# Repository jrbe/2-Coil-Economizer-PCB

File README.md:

**This V1.1 version is not working.  The transistor is flipped on each channel and the DRV103's I got seem to be counterfeit.  Plan is to eventually swap both DRV103's to 556 timers and to a logic ic for flexible input control to reduce cost, eliminate the DRV issues, and simplify the whole project.**

# 2 Coil Economizer PCB
 This 2 Coil DRV103 Economizer PCB is not tested yet. It has at least 1 issue as when its soldered to + triggered the coil output is at 100% with the trigger wire floating. 

It was designed for contactor economizing, for 8-28v, and around 10 amps for each coil. This delivers full power for a short time to pull in the relay or contactor then switches over to a pulse output to conserve power, lower heat, etc. for the coil.

The frequency, duty cycle, and delay info is printed on the bottom of the pc board for reference.

Frequency is set to 25kHz by default.  Its recommended to keep it at 25kHz but can be adjusted from 25kHz down to 20kHz by cutting the 20/25kHz jumpers if required. The 20kHZ mod jumper (follow the silkscreen line to it) must also be soldered to adjust the voltage divider stack to work with the different pwm frequency load requirements of 20kHz for the DRV103 IC.

PWM Duty cycle is set to 21.8% by default, 3 jumpers are shorted on each coil circuit.  This is using voltage to set the duty cycle in the DRV103, a simulation of the circuit is here, https://everycircuit.com/circuit/4973018295828480  These can be cut if necessary.  If more than 21.8% is required more solder jumpers can be soldered.  Which gets cut or soldered doesn't matter as long as its in the silkscreened group. 
Number of jumpers shorted: 0 = 14.3%, 1 = 17%, 2 = 19.75%, 3 = 21.8%, 4 = 23.9%, 5 = 26%, 6 = 28%.  Looking at the top, the left 3 are shorted with a trace across them.

The DRV103 has an adjustable full on time then switches to pwm to hold the coil.  By default all 4 solder jumpers are shorted for a 550ms on time.  These jumpers can be cut to allow less full on time if required. Which gets cut or soldered doesn't matter as long as its in the silkscreened group.
Number of jumpers shorted: 0 = 110ms, 1 = 220ms, 2 = 330ms, 3 = 440ms, 4 = 550ms.

There is a trigger +/- jumper for each coil that needs to be soldered center pad to + or -.  Soldered to + it will turn on the coil with a + signal connected to Coil x trigger.  Soldered to -, it will turn on when the coil trigger is connected to -.  https://everycircuit.com/circuit/4812355044900864 is a simulation of the circuit.

There is an excel file with the calculated values of different DRV103 settings in the references folder.  

The oval slots are oversized for both 5mm and 5.08mm connectors.  This includes Phoenix Contact 1017509, 1751228, 1776260-8, etc. TE 521384-8, Faston tabs, and direct solder.  If direct solder is chosen the "teeth" at the bottom can be used as a strain relief with shrink tubing over them. They are 8mm wide at the bottom.  Small or single wires may require a second layer of shrink tubing.

Testing of the contactors should be done without high voltage connected.  A voltage of 10v or less should be considered for testing to verify the contactors will not accidently open from a low 12v battery. Watching for continuity the coil can be energized and running in pwm mode and hit down on a padded table (simulating a hard bump) with the high voltage terminals up.  There should be no break in continuity and should not open.

Pricey items are the tantalum capacitors that are recommended in the Ti DRV103 datasheet for higher power useage and a few extended JLC components with uncommon resistances.  The DRV103 ICs will likely need to be preordered from JLCPCB or populated later.  

These boards were about $30usd each from JLCPCB at a qty of 5 boards at the time of design.  
Designed in KiCAD 7 
Production files were made using Fabrication Toolkit, https://github.com/bennymeg/Fabrication-Toolkit to correct BOMs, rotations, etc. for JLCPCB.
https://yaqwsx.github.io/jlcparts/#/ was used to find available JLC components.

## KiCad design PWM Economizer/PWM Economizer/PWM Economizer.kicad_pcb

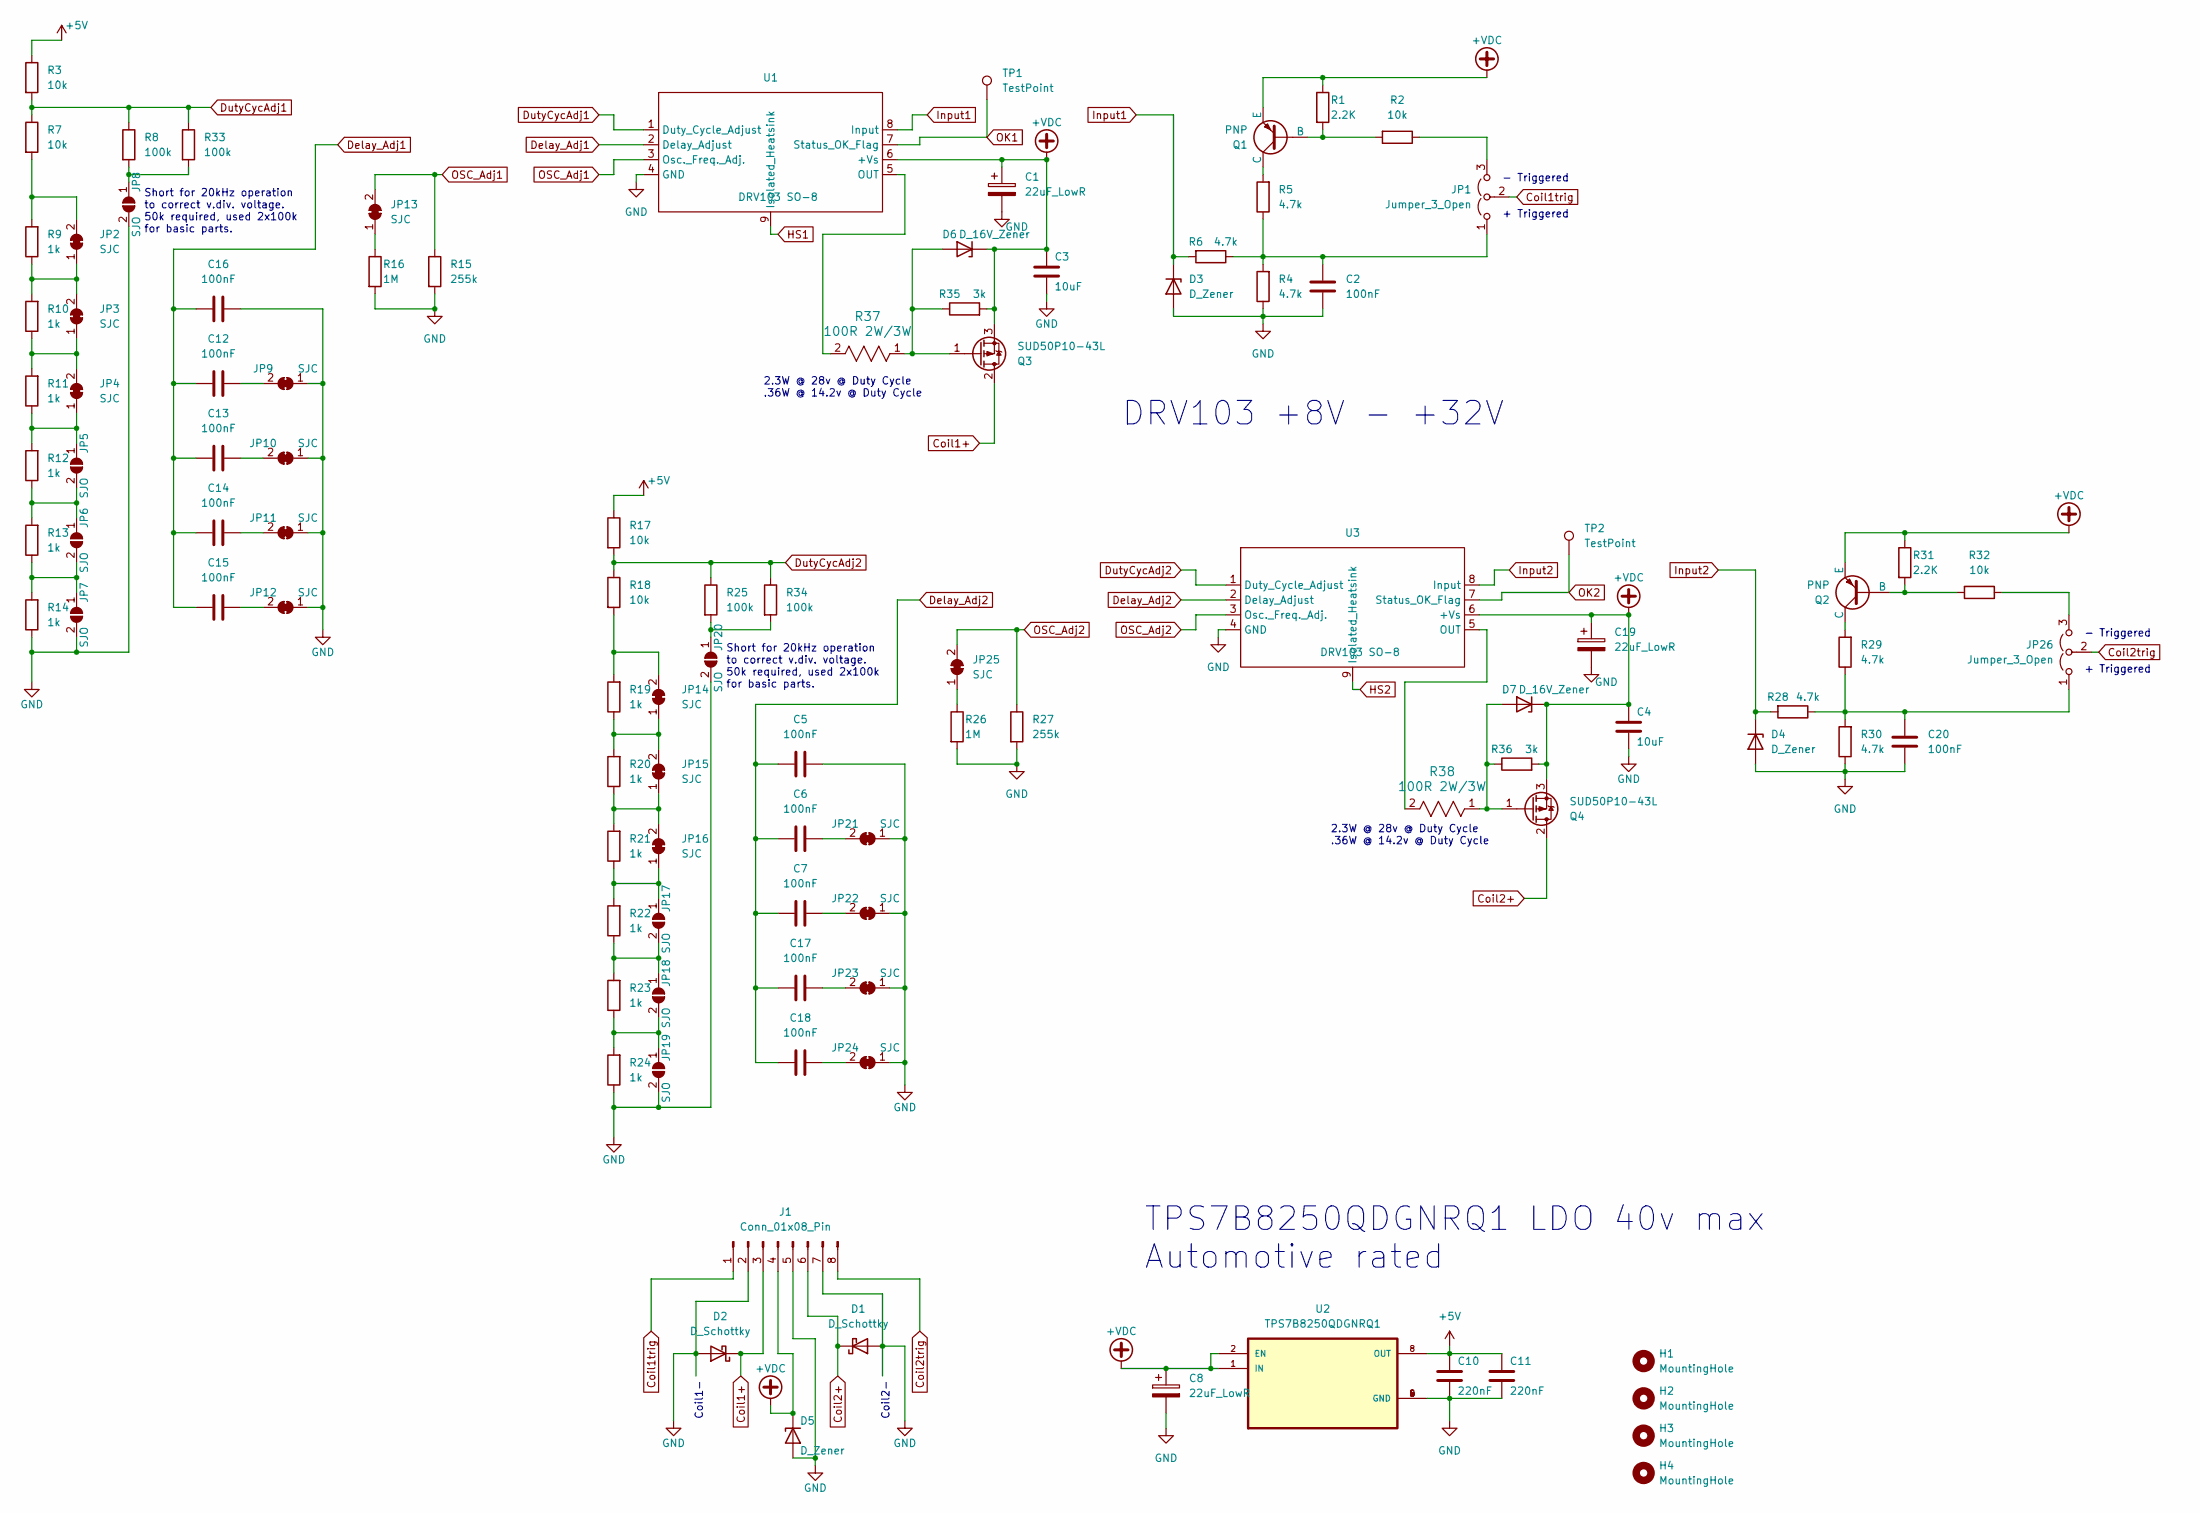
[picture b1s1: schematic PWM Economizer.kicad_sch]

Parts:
C1, C8, C19: 22uF_LowR; CP_EIA-7343-15_Kemet-W_Pad2.25x2.55mm_HandSolder; LCSC Part C2798130
C2, C5, C6, C7, C12, C13, C14, C15, C16, C17, C18, C20: 100nF; C_0805_2012Metric_Pad1.18x1.45mm_HandSolder; LCSC Part C28233
C3, C4: 10uF; C_0805_2012Metric_Pad1.18x1.45mm_HandSolder; LCSC Part C440198
C10, C11: 220nF; C_0805_2012Metric_Pad1.18x1.45mm_HandSolder; LCSC Part C5378
D1, D2: D_Schottky; D_SMA_Handsoldering; LCSC Part C22452
D3, D4: D_Zener; D_SOD-123; LCSC Part C173413
D5: D_Zener; D_SMA; LCSC Part C235776
D6, D7: D_16V_Zener; D_SMB; LCSC Part C2940079
H1, H2, H3, H4: MountingHole; MountingHole_4mm
J1: Conn_01x08_Pin; Multi-Fit_Faston-SolderedWire-5&5.08mmWireToBoardBlock_1x08
JP1, JP26: Jumper_3_Open; SolderJumper-3_P1.3mm_Open_RoundedPad1.0x1.5mm
JP2, JP3, JP4, JP9, JP10, JP11, JP12, JP13, JP14, JP15, JP16, JP21, JP22, JP23, JP24, JP25: SJC; SolderJumper-2_P1.3mm_Bridged_RoundedPad1.0x1.5mm
JP5, JP6, JP7, JP8, JP17, JP18, JP19, JP20: SJO; SolderJumper-2_P1.3mm_Open_RoundedPad1.0x1.5mm
Q1, Q2: PNP; SOT-23; LCSC Part C8326
Q3, Q4: SUD50P10-43L; TO-252-2; LCSC Part C913430
R1, R31: 2.2K; R_0805_2012Metric_Pad1.20x1.40mm_HandSolder; LCSC Part C17520
R2, R3, R7, R17, R18, R32: 10k; R_0805_2012Metric_Pad1.20x1.40mm_HandSolder; LCSC Part C17414
R4, R5, R6, R28, R29, R30: 4.7k; R_0805_2012Metric_Pad1.20x1.40mm_HandSolder; LCSC Part C17673
R8, R25, R33, R34: 100k; R_0805_2012Metric_Pad1.20x1.40mm_HandSolder; Manufacturer Part No. ARG05DTC5002; LCSC Part C2828840
R9, R10, R11, R12, R13, R14, R19, R20, R21, R22, R23, R24: 1k; R_0805_2012Metric_Pad1.20x1.40mm_HandSolder; Manufacturer Part No. RC0805JR-071M5L; LCSC Part C17513
R15, R27: 255k; R_0805_2012Metric_Pad1.20x1.40mm_HandSolder; Manufacturer Part No. SCR0805F255K; LCSC Part C3016493
R16, R26: 1M; R_0805_2012Metric_Pad1.20x1.40mm_HandSolder; LCSC Part C17514
R35, R36: 3k; R_0805_2012Metric_Pad1.20x1.40mm_HandSolder; Manufacturer Part No. 0805W8F3001T5E; LCSC Part C17661
R37, R38: 100R 2W/3W; SMD_Res 3W 12x5.8 & 2512; LCSC Part C309610
TP1, TP2: TestPoint; TestPoint_THTPad_1.0x1.0mm_Drill0.5mm
U1, U3: DRV103 SO-8; DRV103 No Heatsink; Manufacturer Part No. DRV103U; LCSC Part C1879940
U2: TPS7B8250QDGNRQ1; SOP65P490X110-9N; Manufacturer Part No. TPS7B8250QDGNRQ1; LCSC Part C424924

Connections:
+5V: C10.1, C11.1, R3.1, R17.1, U2.8 (OUT)
+VDC: C1.1, C3.1, C4.1, C8.1, C19.1, D5.1 (K), D6.1 (K), D7.1 (K), J1.4, Q1.3 (E), Q2.3 (E), Q3.3 (S), Q4.3 (S), R1.1, R31.1, R35.2, R36.2, U1.6 (+Vs), U2.1 (IN), U2.2 (EN), U3.6 (+Vs)
Coil1+: D2.1 (K), J1.3, Q3.2 (D)
Coil1trig: J1.1, JP1.2 (C)
Coil2+: D1.1 (K), J1.6, Q4.2 (D)
Coil2trig: J1.8, JP26.2 (C)
Delay_Adj1: C12.1, C13.1, C14.1, C15.1, C16.1, U1.2 (Delay_Adjust)
Delay_Adj2: C5.1, C6.1, C7.1, C17.1, C18.1, U3.2 (Delay_Adjust)
DutyCycAdj1: R3.2, R7.1, R8.1, R33.1, U1.1 (Duty_Cycle_Adjust)
DutyCycAdj2: R17.2, R18.1, R25.1, R34.1, U3.1 (Duty_Cycle_Adjust)
GND: C1.2, C2.2, C3.2, C4.2, C5.2, C8.2, C10.2, C11.2, C16.2, C19.2, C20.2, D1.2 (A), D2.2 (A), D3.2 (A), D4.2 (A), D5.2 (A), J1.2, J1.5, J1.7, JP7.2 (B), JP8.2 (B), JP9.1 (A), JP10.1 (A), JP11.1 (A), JP12.1 (A), JP19.2 (B), JP20.2 (B), JP21.1 (A), JP22.1 (A), JP23.1 (A), JP24.1 (A), R4.1, R14.1, R15.2, R16.2, R24.1, R26.2, R27.2, R30.1, U1.4 (GND), U2.4 (GND), U2.5 (GND), U2.6 (GND), U2.9 (GND), U3.4 (GND)
Input1: D3.1 (K), R6.2, U1.8 (Input)
Input2: D4.1 (K), R28.2, U3.8 (Input)
unnamed: D6.2 (A), Q3.1 (G), R35.1, R37.1
unnamed: D7.2 (A), Q4.1 (G), R36.1, R38.1
unnamed: C2.1, JP1.1 (A), R4.2, R5.1, R6.1
unnamed: JP1.3 (B), R2.1
unnamed: JP2.1 (A), JP3.2 (B), R9.1, R10.2
unnamed: JP2.2 (B), R7.2, R9.2
unnamed: JP3.1 (A), JP4.2 (B), R10.1, R11.2
unnamed: JP4.1 (A), JP5.1 (A), R11.1, R12.2
unnamed: JP5.2 (B), JP6.1 (A), R12.1, R13.2
unnamed: JP6.2 (B), JP7.1 (A), R13.1, R14.2
unnamed: JP8.1 (A), R8.2, R33.2
unnamed: C12.2, JP9.2 (B)
unnamed: C13.2, JP10.2 (B)
unnamed: C14.2, JP11.2 (B)
unnamed: C15.2, JP12.2 (B)
unnamed: JP13.1 (A), R16.1
unnamed: JP14.1 (A), JP15.2 (B), R19.1, R20.2
unnamed: JP14.2 (B), R18.2, R19.2
unnamed: JP15.1 (A), JP16.2 (B), R20.1, R21.2
unnamed: JP16.1 (A), JP17.1 (A), R21.1, R22.2
unnamed: JP17.2 (B), JP18.1 (A), R22.1, R23.2
unnamed: JP18.2 (B), JP19.1 (A), R23.1, R24.2
unnamed: JP20.1 (A), R25.2, R34.2
unnamed: C6.2, JP21.2 (B)
unnamed: C7.2, JP22.2 (B)
unnamed: C17.2, JP23.2 (B)
unnamed: C18.2, JP24.2 (B)
unnamed: JP25.1 (A), R26.1
unnamed: C20.1, JP26.1 (A), R28.1, R29.1, R30.2
unnamed: JP26.3 (B), R32.1
unnamed: Q1.2 (B), R1.2, R2.2
unnamed: Q1.1 (C), R5.2
unnamed: Q2.2 (B), R31.2, R32.2
unnamed: Q2.1 (C), R29.2
unnamed: R37.2, U1.5 (OUT)
unnamed: R38.2, U3.5 (OUT)
OK1: TP1.1, U1.7 (Status_OK_Flag)
OK2: TP2.1, U3.7 (Status_OK_Flag)
OSC_Adj1: JP13.2 (B), R15.1, U1.3 (Osc._Freq._Adj.)
OSC_Adj2: JP25.2 (B), R27.1, U3.3 (Osc._Freq._Adj.)

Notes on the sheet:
Short for 20kHz operation to correct v.div. voltage. 50k required, used 2x100k for basic parts.
Coil2-
2.3W @ 28v @ Duty Cycle .36W @ 14.2v @ Duty Cycle
- Triggered + Triggered
Coil1-
DRV103 +8V - +32V
TPS7B8250QDGNRQ1 LDO 40v max Automotive rated

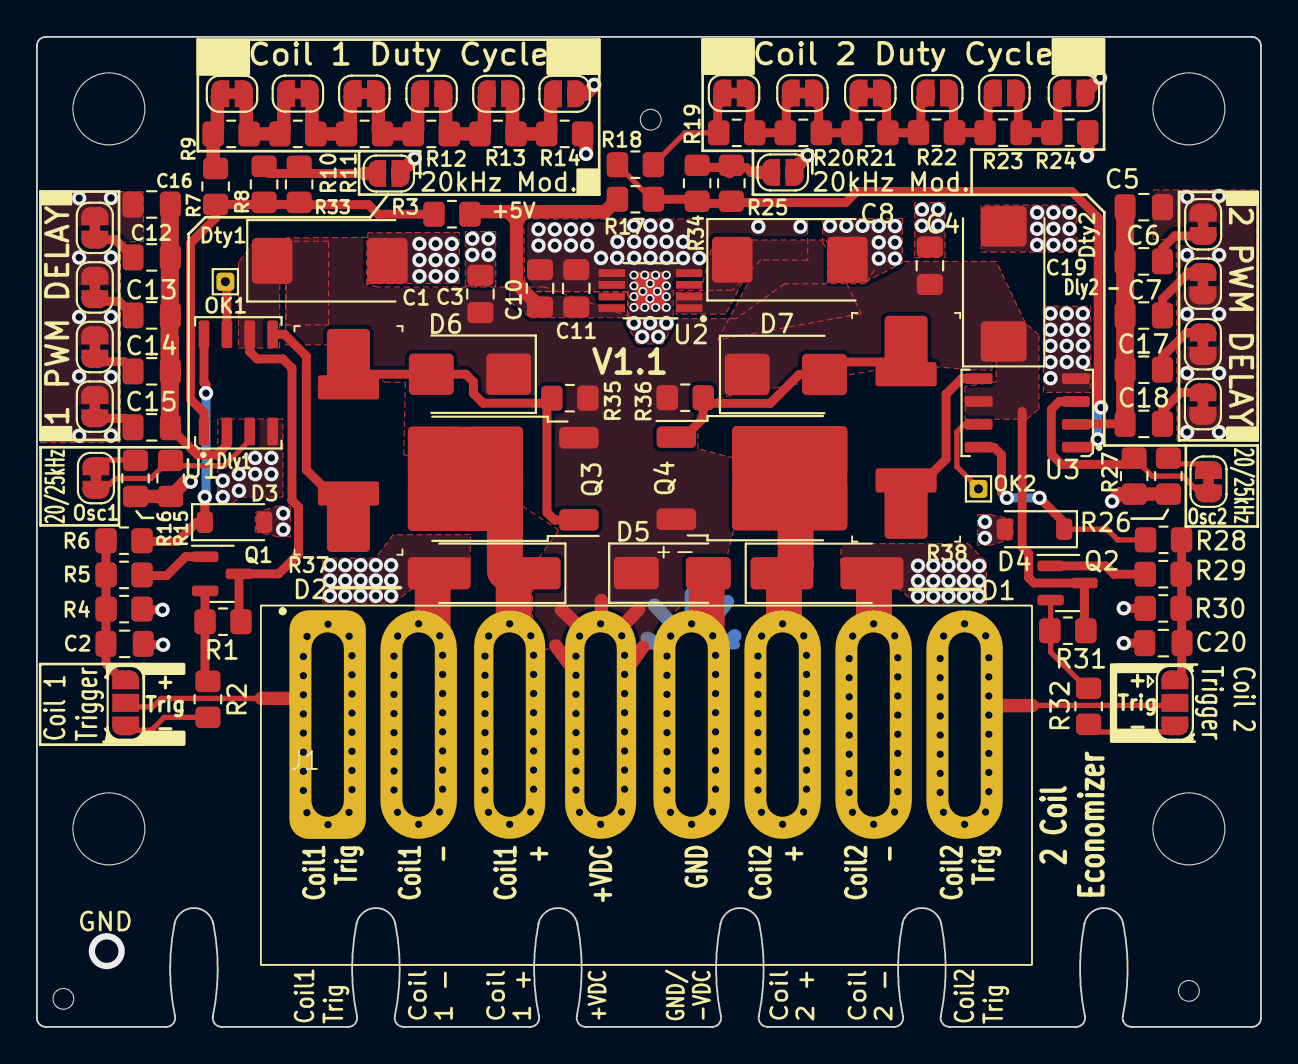
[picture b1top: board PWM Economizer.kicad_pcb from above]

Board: 2 copper layers, 68.0 x 55.0 mm, 104 parts (0 on the bottom side), 53 nets.

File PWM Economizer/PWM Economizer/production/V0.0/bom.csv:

Designator,Footprint,Quantity,Value,LCSC Part #
"C1, C19, C8",CP_EIA-7343-15_Kemet-W_Pad2.25x2.55mm_HandSolder,3,22uF_LowR,C1952730
"C10, C11",0805,2,220nF,C5378
"C12, C13, C14, C15, C16, C17, C18, C2, C20, C5, C6, C7",0805,12,100nF,C28233
"C3, C4",0805,2,10uF,C440198
"D1, D2",D_SMA_Handsoldering,2,D_Schottky,C22452
"D3, D4",D_SOD-123,2,D_Zener,C173413
D5,D_SMA,1,D_Zener,C235776
"H1, H2, H3, H4",MountingHole_4mm,4,MountingHole,
J1,Multi-Fit_Faston-SolderedWire-5&5.08mmWireToBoardBlock_1x08,1,Conn_01x08_Pin,
"JP1, JP26",SolderJumper-3_P1.3mm_Open_RoundedPad1.0x1.5mm,2,Jumper_3_Open,
"JP10, JP11, JP12, JP13, JP14, JP15, JP16, JP2, JP21, JP22, JP23, JP24, JP25, JP3, JP4, JP9",SolderJumper-2_P1.3mm_Bridged_RoundedPad1.0x1.5mm,16,SJC,
"JP17, JP18, JP19, JP20, JP5, JP6, JP7, JP8",SolderJumper-2_P1.3mm_Open_RoundedPad1.0x1.5mm,8,SJO,
"Q1, Q2",SOT-23,2,PNP,C516596
"R1, R31",0805,2,2.2K,C17520
"R10, R11, R12, R13, R14, R19, R20, R21, R22, R23, R24, R9",0805,12,1k,C17513
"R15, R27",0805,2,255k,C3016493
"R16, R26",0805,2,1M,C137463
"R17, R18, R2, R3, R32, R7",0805,6,10k,C17414
"R25, R33, R34, R8",0805,4,100k,C2828840
"R28, R29, R30, R4, R5, R6",0805,6,4.7k,C17673
"TP1, TP2",TestPoint_THTPad_1.0x1.0mm_Drill0.5mm,2,TestPoint,
"U1, U3",DRV103 PowerPad SOIC Large Heatsink,2,DRV103 SO-8,C1556557
U2,SOP65P490X110-9N,1,TPS7B8250QDGNRQ1,C424924

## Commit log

2024-04-25 Uploading
    Uploading
2024-04-25 Update README.md
    Corrected spelling
2024-08-15 V1.1 Untested
    V1.1 Untested
